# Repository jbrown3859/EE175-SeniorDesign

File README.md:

# EE175-SeniorDesign
Joey Brown, jbrow123 at ucr dot edu  
Merrick Slane, mslan002 at ucr dot edu  
Vincent Le, vle059 at ucr dot edu  

[Google Drive with more material](https://drive.google.com/drive/folders/17umrwFU26v1C86p7LwNFVo5_QjvbGcJk?usp=sharing)

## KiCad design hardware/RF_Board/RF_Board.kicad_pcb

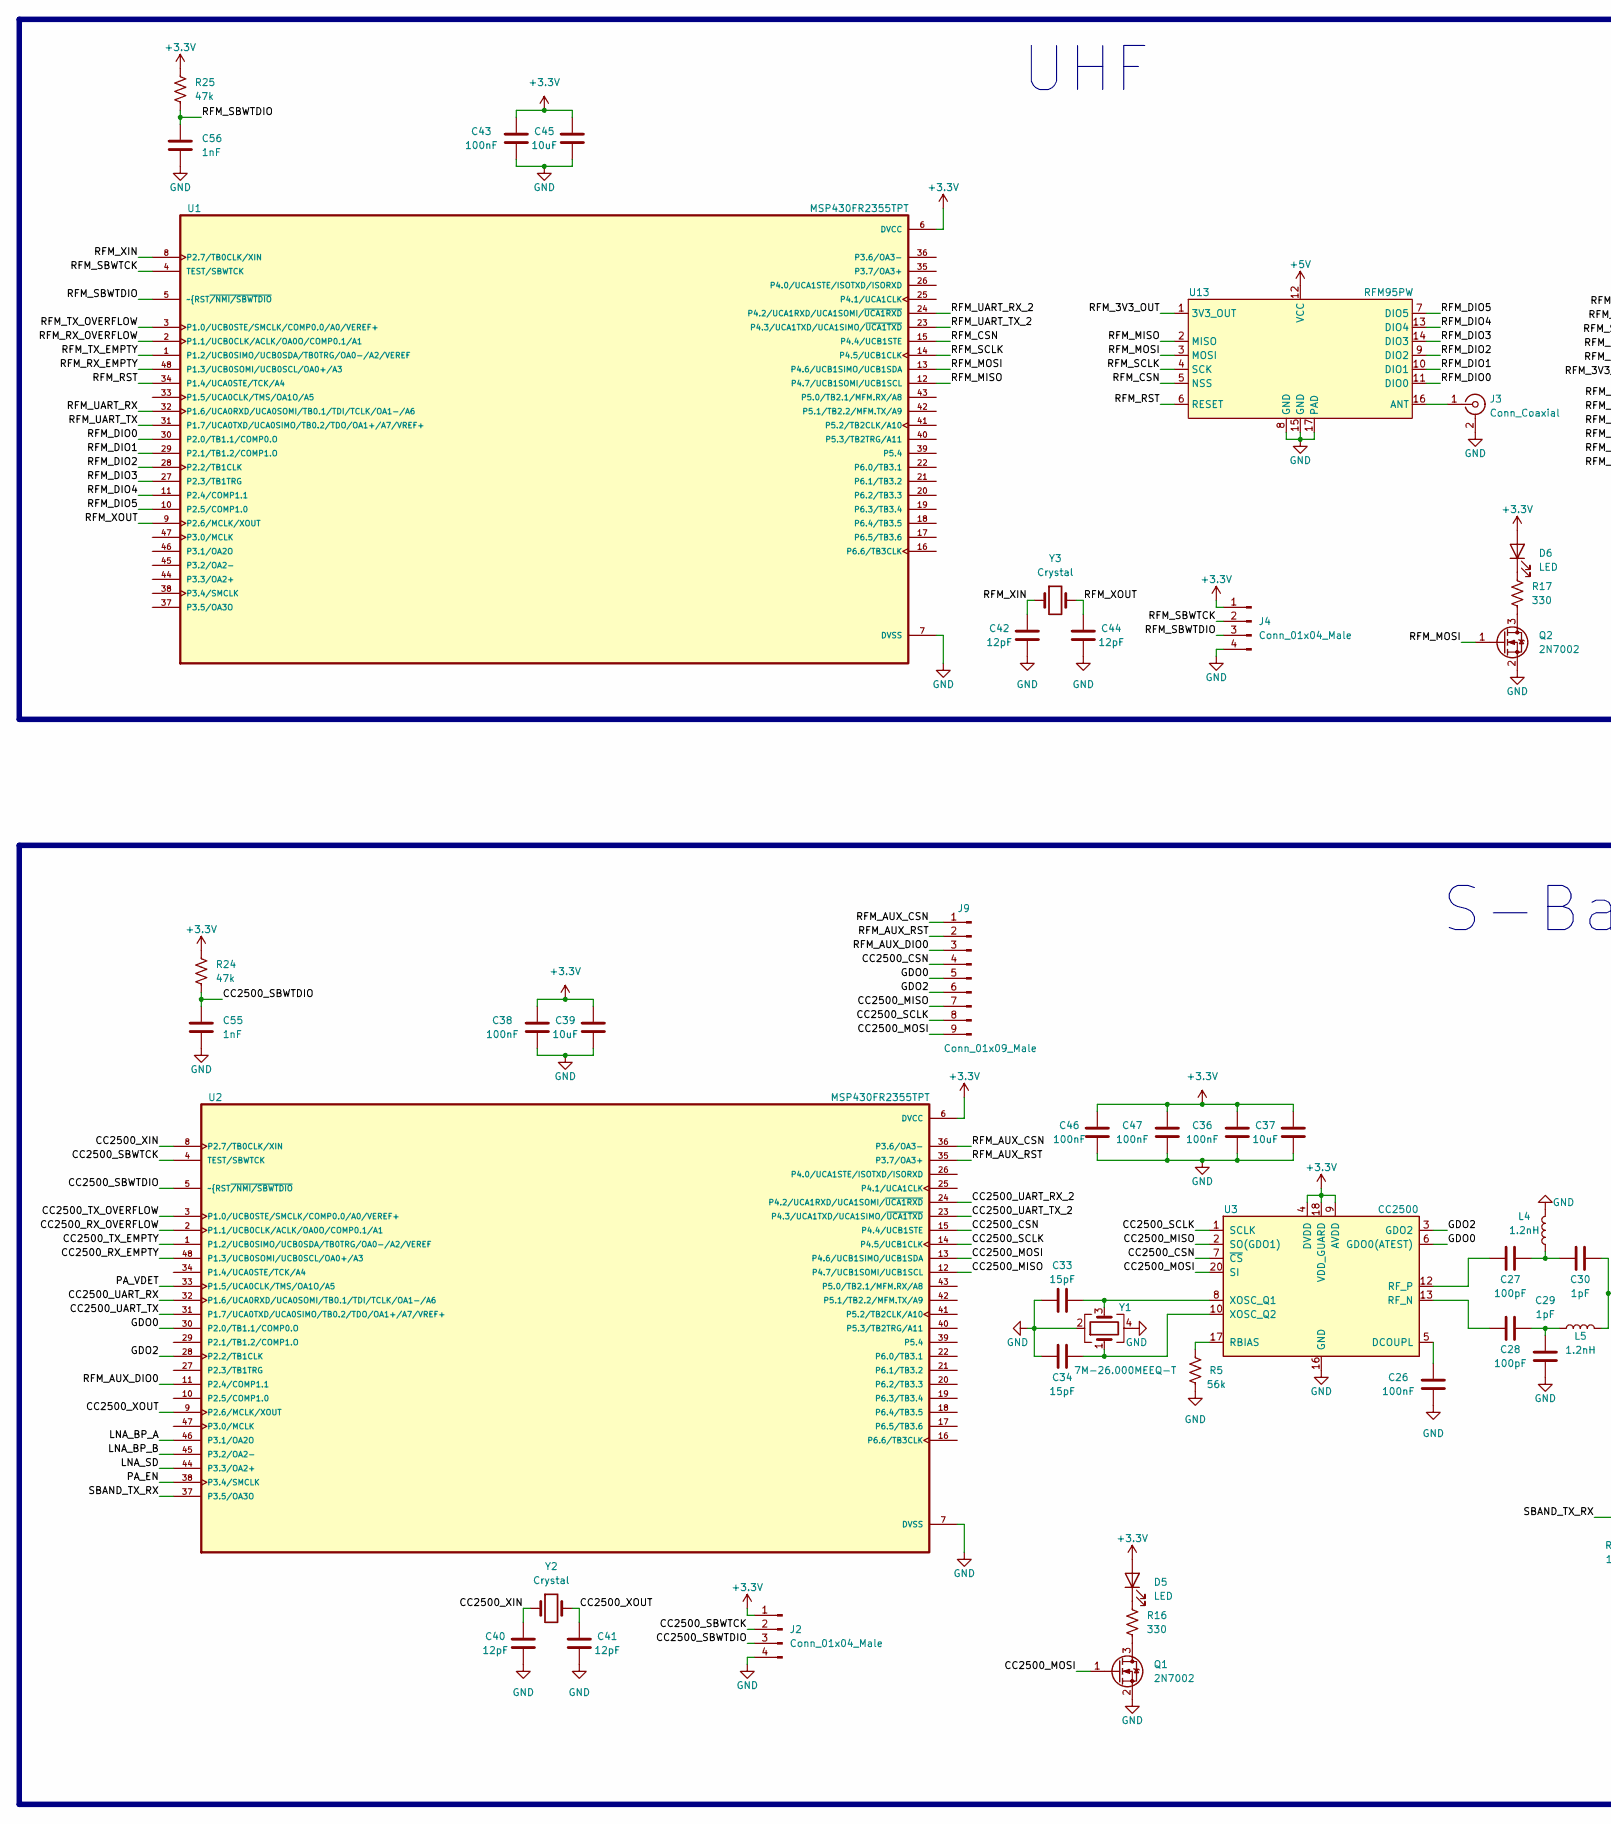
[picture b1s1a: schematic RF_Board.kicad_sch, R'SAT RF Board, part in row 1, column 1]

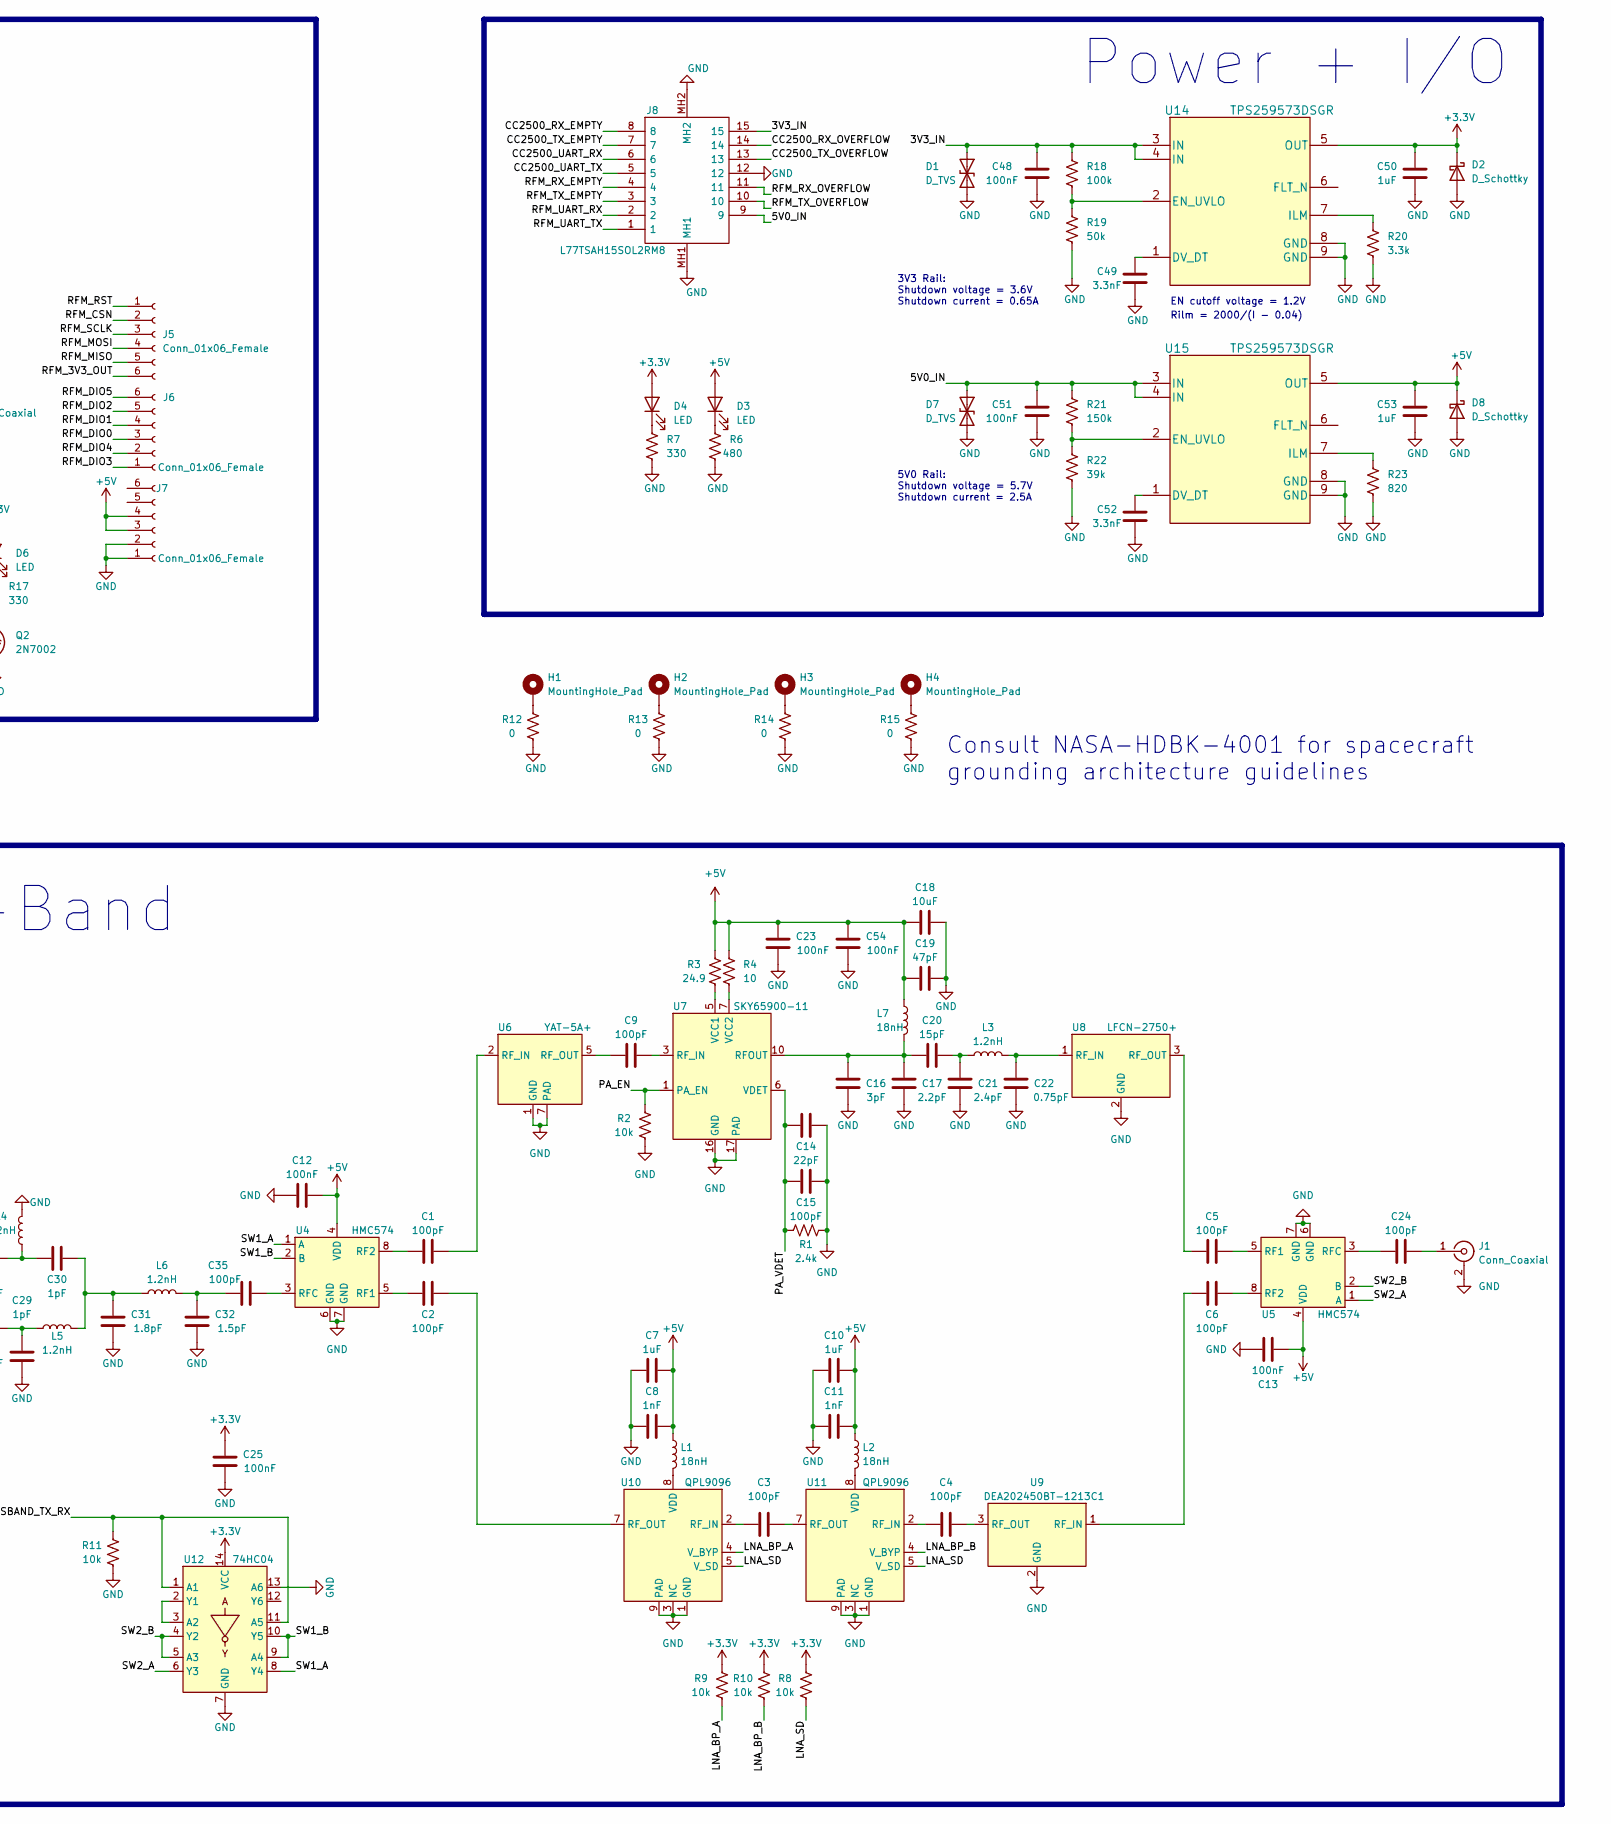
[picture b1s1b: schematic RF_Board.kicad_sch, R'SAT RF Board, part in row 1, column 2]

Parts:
C1, C2, C3, C4, C5, C6, C9, C24, C27, C28, C35: 100pF; C_0402_1005Metric
C7, C10, C50, C53: 1uF; C_0805_2012Metric
C8, C11, C55, C56: 1nF; C_0603_1608Metric
C12, C13, C23, C25, C26, C36, C38, C43, C46, C47, C48, C51, C54: 100nF; C_0603_1608Metric
C14: 22pF; C_0603_1608Metric
C15: 100pF; C_0603_1608Metric
C16: 3pF; C_0402_1005Metric
C17: 2.2pF; C_0402_1005Metric
C18, C37, C39, C45: 10uF; C_1206_3216Metric
C19: 47pF; C_0603_1608Metric
C20: 15pF; C_0402_1005Metric
C21: 2.4pF; C_0402_1005Metric
C22: 0.75pF; C_0402_1005Metric
C29, C30: 1pF; C_0402_1005Metric
C31: 1.8pF; C_0402_1005Metric
C32: 1.5pF; C_0402_1005Metric
C33, C34: 15pF; C_0603_1608Metric
C40, C41, C42, C44: 12pF; C_0603_1608Metric
C49, C52: 3.3nF; C_0603_1608Metric
D1, D7: D_TVS; SOD882
D2, D8: D_Schottky; D_SOD-523
D3, D4, D5, D6: LED; LED_0603_1608Metric
H1, H2, H3, H4: MountingHole_Pad; MountingHole_4.3mm_M4_Pad_Via
J1, J3: Conn_Coaxial; SMA_Amphenol_901-144_Vertical
J2, J4: Conn_01x04_Male; PinHeader_1x04_P2.54mm_Vertical
J5, J6, J7: Conn_01x06_Female; PinHeader_1x06_P2.54mm_Vertical
J8: L77TSAH15SOL2RM8; Mouser Part Number 523-L77TSAH15SOL2RM8
J9: Conn_01x09_Male; PinHeader_1x09_P2.54mm_Vertical
L1, L2, L7: 18nH; L_0603_1608Metric
L3, L4, L5, L6: 1.2nH; L_0402_1005Metric
Q1, Q2: 2N7002; SOT-23
R1: 2.4k; R_0603_1608Metric
R2, R8, R9, R10, R11: 10k; R_0603_1608Metric
R3: 24.9; R_0603_1608Metric
R4: 10; R_0603_1608Metric
R5: 56k; C_0603_1608Metric
R6: 480; R_0603_1608Metric
R7, R16, R17: 330; R_0603_1608Metric
R12, R13, R14, R15: 0; R_0603_1608Metric
R18: 100k; R_0402_1005Metric
R19: 50k; R_0402_1005Metric
R20: 3.3k; R_0402_1005Metric
R21: 150k; R_0402_1005Metric
R22: 39k; R_0402_1005Metric
R23: 820; R_0402_1005Metric
R24, R25: 47k; R_0603_1608Metric
U1, U2: MSP430FR2355TPT; QFP50P900X900X160-48N
U3: CC2500; Texas_S-PVQFN-N20_EP2.4x2.4mm
U4, U5: HMC574; HMC574AMS8E
U6: YAT-5A+; YAT-1A&plus_
U7: SKY65900-11; QFN-16-1EP_4x4mm_P0.65mm_EP2.5x2.5mm
U8: LFCN-2750+; LFCN-2500&plus_
U9: DEA202450BT-1213C1
U10, U11: QPL9096; QPL9504TR7
U12: 74HC04; SOIC-14_3.9x8.7mm_P1.27mm
U13: RFM95PW
U14, U15: TPS259573DSGR; DSG0008A
Y1: 7M-26.000MEEQ-T; Crystal_SMD_3225-4Pin_3.2x2.5mm
Y2, Y3: Crystal; ECS-.327-12.5-34B-TR

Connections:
+3.3V: C25.1, C36.1, C37.2, C38.1, C39.2, C43.1, C45.2, C46.2, C47.1, C50.2, D2.1 (K), D4.2 (A), D5.2 (A), D6.2 (A), J2.1, J4.1, R8.1, R9.1, R10.1, R24.1, R25.1, U1.6 (DVCC), U2.6 (DVCC), U3.4 (DVDD), U3.9 (AVDD), U3.11 (AVDD), U3.14 (AVDD), U3.15 (AVDD), U3.18 (VDD_GUARD), U12.14 (VCC), U14.5 (OUT)
+5V: C7.2, C8.2, C10.2, C11.2, C12.1, C13.1, C18.1, C19.1, C23.1, C53.2, C54.1, D3.2 (A), D8.1 (K), J7.3, J7.4, L1.1, L2.1, L7.1, R3.1, R4.2, U4.4 (VDD), U5.4 (VDD), U13.12 (VCC), U15.5 (OUT)
/3V3_IN: C48.1, D1.1 (A1), J8.15, R18.1, U14.3 (IN), U14.4 (IN)
/5V0_IN: C51.1, D7.1 (A1), J8.9, R21.1, U15.3 (IN), U15.4 (IN)
/CC2500_CSN: J9.4, U2.15 (P4.4/UCB1STE), U3.7 (~CS)
/CC2500_MISO: J9.7, U2.12 (P4.7/UCB1SOMI/UCB1SCL), U3.2 (SO(GDO1))
/CC2500_MOSI: J9.9, Q1.1 (G), U2.13 (P4.6/UCB1SIMO/UCB1SDA), U3.20 (SI)
/CC2500_RX_EMPTY: J8.8, U2.48 (P1.3/UCB0SOMI/UCB0SCL/OA0+/A3)
/CC2500_RX_OVERFLOW: J8.14, U2.2 (P1.1/UCB0CLK/ACLK/OA0O/COMP0.1/A1)
/CC2500_SBWTCK: J2.2, U2.4 (TEST/SBWTCK)
/CC2500_SBWTDIO: C55.1, J2.3, R24.2, U2.5 (~RST~{/NMI/SBWTDIO)
/CC2500_SCLK: J9.8, U2.14 (P4.5/UCB1CLK), U3.1 (SCLK)
/CC2500_TX_EMPTY: J8.7, U2.1 (P1.2/UCB0SIMO/UCB0SDA/TB0TRG/OA0-/A2/VE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)
/CC2500_TX_OVERFLOW: J8.13, U2.3 (P1.0/UCB0STE/SMCLK/COMP0.0/A0/VEREF+)
/CC2500_UART_RX: J8.6, U2.32 (P1.6/UCA0RXD/UCA0SOMI/TB0.1/TDI/TCLK/OA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)
/CC2500_UART_RX_2: U2.24 (P4.2/UCA1RXD/UCA1SOMI/~UCA1RXD)
/CC2500_UART_TX: J8.5, U2.31 (P1.7/UCA0TXD/UCA0SIMO/TB0.2/TDO/OA1+/A7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)
/CC2500_UART_TX_2: U2.23 (P4.3/UCA1TXD/UCA1SIMO/~UCA1TXD)
/CC2500_XIN: C40.2, U2.8 (P2.7/TB0CLK/XIN), Y2.1
/CC2500_XOUT: C41.2, U2.9 (P2.6/MCLK/XOUT), Y2.2
/GDO0: J9.5, U2.30 (P2.0/TB1.1/COMP0.O), U3.6 (GDO0(ATEST))
/GDO2: J9.6, U2.28 (P2.2/TB1CLK), U3.3 (GDO2)
/LNA_BP_A: R9.2, U2.46 (P3.1/OA2O), U10.4 (V_BYP)
/LNA_BP_B: R10.2, U2.45 (P3.2/OA2-), U11.4 (V_BYP)
/LNA_SD: R8.2, U2.44 (P3.3/OA2+), U10.5 (V_SD), U11.5 (V_SD)
/PA_EN: R2.1, U2.38 (P3.4/SMCLK), U7.1 (PA_EN)
/PA_VDET: C14.1, C15.1, R1.1, U2.33 (P1.5/UCA0CLK/TMS/OA1O/A5), U7.6 (VDET)
/RFM_3V3_OUT: J5.6, U13.1 (3V3_OUT)
/RFM_AUX_CSN: J9.1, U2.36 (P3.6/OA3-)
/RFM_AUX_DIO0: J9.3, U2.11 (P2.4/COMP1.1)
/RFM_AUX_RST: J9.2, U2.35 (P3.7/OA3+)
/RFM_CSN: J5.2, U1.15 (P4.4/UCB1STE), U13.5 (NSS)
/RFM_DIO0: J6.3, U1.30 (P2.0/TB1.1/COMP0.O), U13.11 (DIO0)
/RFM_DIO1: J6.4, U1.29 (P2.1/TB1.2/COMP1.O), U13.10 (DIO1)
/RFM_DIO2: J6.5, U1.28 (P2.2/TB1CLK), U13.9 (DIO2)
/RFM_DIO3: J6.1, U1.27 (P2.3/TB1TRG), U13.14 (DIO3)
/RFM_DIO4: J6.2, U1.11 (P2.4/COMP1.1), U13.13 (DIO4)
/RFM_DIO5: J6.6, U1.10 (P2.5/COMP1.0), U13.7 (DIO5)
/RFM_MISO: J5.5, U1.12 (P4.7/UCB1SOMI/UCB1SCL), U13.2 (MISO)
/RFM_MOSI: J5.4, Q2.1 (G), U1.13 (P4.6/UCB1SIMO/UCB1SDA), U13.3 (MOSI)
/RFM_RST: J5.1, U1.34 (P1.4/UCA0STE/TCK/A4), U13.6 (RESET)
/RFM_RX_EMPTY: J8.4, U1.48 (P1.3/UCB0SOMI/UCB0SCL/OA0+/A3)
/RFM_RX_OVERFLOW: J8.11, U1.2 (P1.1/UCB0CLK/ACLK/OA0O/COMP0.1/A1)
/RFM_SBWTCK: J4.2, U1.4 (TEST/SBWTCK)
/RFM_SBWTDIO: C56.1, J4.3, R25.2, U1.5 (~RST~{/NMI/SBWTDIO)
/RFM_SCLK: J5.3, U1.14 (P4.5/UCB1CLK), U13.4 (SCK)
/RFM_TX_EMPTY: J8.3, U1.1 (P1.2/UCB0SIMO/UCB0SDA/TB0TRG/OA0-/A2/VE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)
/RFM_TX_OVERFLOW: J8.10, U1.3 (P1.0/UCB0STE/SMCLK/COMP0.0/A0/VEREF+)
/RFM_UART_RX: J8.2, U1.32 (P1.6/UCA0RXD/UCA0SOMI/TB0.1/TDI/TCLK/OA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)
/RFM_UART_RX_2: U1.24 (P4.2/UCA1RXD/UCA1SOMI/~UCA1RXD)
/RFM_UART_TX: J8.1, U1.31 (P1.7/UCA0TXD/UCA0SIMO/TB0.2/TDO/OA1+/A7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)
/RFM_UART_TX_2: U1.23 (P4.3/UCA1TXD/UCA1SIMO/~UCA1TXD)
/RFM_XIN: C42.2, U1.8 (P2.7/TB0CLK/XIN), Y3.1; also elsewhere on the board
/RFM_XOUT: C44.2, U1.9 (P2.6/MCLK/XOUT), Y3.2; also elsewhere on the board
/SBAND_TX_RX: R11.1, U2.37 (P3.5/OA3O), U12.1 (A1), U12.11 (A5)
/SW1_A: U4.1 (A), U12.8 (Y4)
/SW1_B: U4.2 (B), U12.9 (A4), U12.10 (Y5)
/SW2_A: U5.1 (A), U12.6 (Y3)
/SW2_B: U5.2 (B), U12.4 (Y2), U12.5 (A3)
GND: C7.1, C8.1, C10.1, C11.1, C12.2, C13.2, C14.2, C15.2, C16.2, C17.2, C18.2, C19.2, C21.1, C22.1, C23.2, C25.2, C26.2, C29.1, C31.1, C32.1, C33.1, C34.1, C36.2, C37.1, C38.2, C39.1, C40.1, C41.1, C42.1, C43.2, C44.1, C45.1, C46.1, C47.2, C48.2, C49.2, C50.1, C51.2, C52.2, C53.1, C54.2, C55.2, C56.2, D1.2 (A2), D2.2 (A), D7.2 (A2), D8.2 (A), J1.2 (Ext), J2.4, J3.2 (Ext), J4.4, J7.1, J7.2, J8.12, J8.MH1, J8.MH2, L4.2, Q1.2 (S), Q2.2 (S), R1.2, R2.2, R5.2, R6.2, R7.2, R11.2, R12.2, R13.2, R14.2, R15.2, R19.2, R20.2, R22.2, R23.2, U1.7 (DVSS), U2.7 (DVSS), U3.16 (GND), U3.19 (GND), U3.21 (GND), U4.6 (GND), U4.7 (GND), U5.6 (GND), U5.7 (GND), U6.1 (GND), U6.3 (GND), U6.4 (GND), U6.6 (GND), U6.7 (PAD), U7.2 (GND), U7.4 (GND), U7.8 (GND), U7.9 (GND), U7.12 (GND), U7.13 (GND), U7.14 (GND), U7.15 (GND), U7.16 (GND), U7.17 (PAD), U8.2 (GND), U8.4 (GND), U9.2 (GND), U9.4 (GND), U10.1 (GND), U10.3 (NC), U10.6 (GND), U10.9 (PAD), U11.1 (GND), U11.3 (NC), U11.6 (GND), U11.9 (PAD), U12.7 (GND), U12.13 (A6), U13.8 (GND), U13.15 (GND), U13.17 (PAD), U14.8 (GND), U14.9 (GND), U15.8 (GND), U15.9 (GND), Y1.2, Y1.4
unnamed: C1.1, U4.8 (RF2)
unnamed: C1.2, U6.2 (RF_IN)
unnamed: C2.1, U4.5 (RF1)
unnamed: C2.2, U10.7 (RF_OUT)
unnamed: C3.1, U10.2 (RF_IN)
unnamed: C3.2, U11.7 (RF_OUT)
unnamed: C4.1, U11.2 (RF_IN)
unnamed: C4.2, U9.3 (RF_OUT)
unnamed: C5.1, U8.3 (RF_OUT)
unnamed: C5.2, U5.5 (RF1)
unnamed: C6.1, U9.1 (RF_IN)
unnamed: C6.2, U5.8 (RF2)
unnamed: C9.1, U6.5 (RF_OUT)
unnamed: C9.2, U7.3 (RF_IN)
unnamed: C16.1, C17.1, C20.1, L7.2, U7.10 (RFOUT), U7.11 (RFOUT)
unnamed: C20.2, C21.2, L3.1
unnamed: C22.2, L3.2, U8.1 (RF_IN)
unnamed: C24.1, U5.3 (RFC)
unnamed: C24.2, J1.1 (In)
unnamed: C26.1, U3.5 (DCOUPL)
unnamed: C27.1, U3.12 (RF_P)
unnamed: C27.2, C30.1, L4.1
unnamed: C28.1, U3.13 (RF_N)
unnamed: C28.2, C29.2, L5.1
unnamed: C30.2, C31.2, L5.2, L6.1
unnamed: C32.2, C35.1, L6.2
unnamed: C35.2, U4.3 (RFC)
unnamed: C49.1, U14.1 (DV_DT)
unnamed: C52.1, U15.1 (DV_DT)
unnamed: D3.1 (K), R6.1
unnamed: D4.1 (K), R7.1
unnamed: D5.1 (K), R16.1
unnamed: D6.1 (K), R17.1
unnamed: H1.1, R12.1
unnamed: H2.1, R13.1
unnamed: H3.1, R14.1
unnamed: H4.1, R15.1
unnamed: J3.1 (In), U13.16 (ANT)
unnamed: L1.2, U10.8 (VDD)
unnamed: L2.2, U11.8 (VDD)
unnamed: Q1.3 (D), R16.2
unnamed: Q2.3 (D), R17.2
unnamed: R3.2, U7.5 (VCC1)
unnamed: R4.1, U7.7 (VCC2)
unnamed: R5.1, U3.17 (RBIAS)
unnamed: R18.2, R19.1, U14.2 (EN_UVLO)
unnamed: R20.1, U14.7 (ILM)
unnamed: R21.2, R22.1, U15.2 (EN_UVLO)
unnamed: R23.1, U15.7 (ILM)
unnamed: C34.2, U3.10 (XOSC_Q2), Y1.1
unnamed: U12.2 (Y1), U12.3 (A2)
unnamed: C33.2, U3.8 (XOSC_Q1), Y1.3

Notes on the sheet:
S-Band
Rilm = 2000/(I - 0.04)
5V0 Rail: Shutdown voltage = 5.7V Shutdown current = 2.5A
EN cutoff voltage = 1.2V
Consult NASA-HDBK-4001 for spacecraft grounding architecture guidelines
Power + I/O
3V3 Rail: Shutdown voltage = 3.6V Shutdown current = 0.65A
UHF

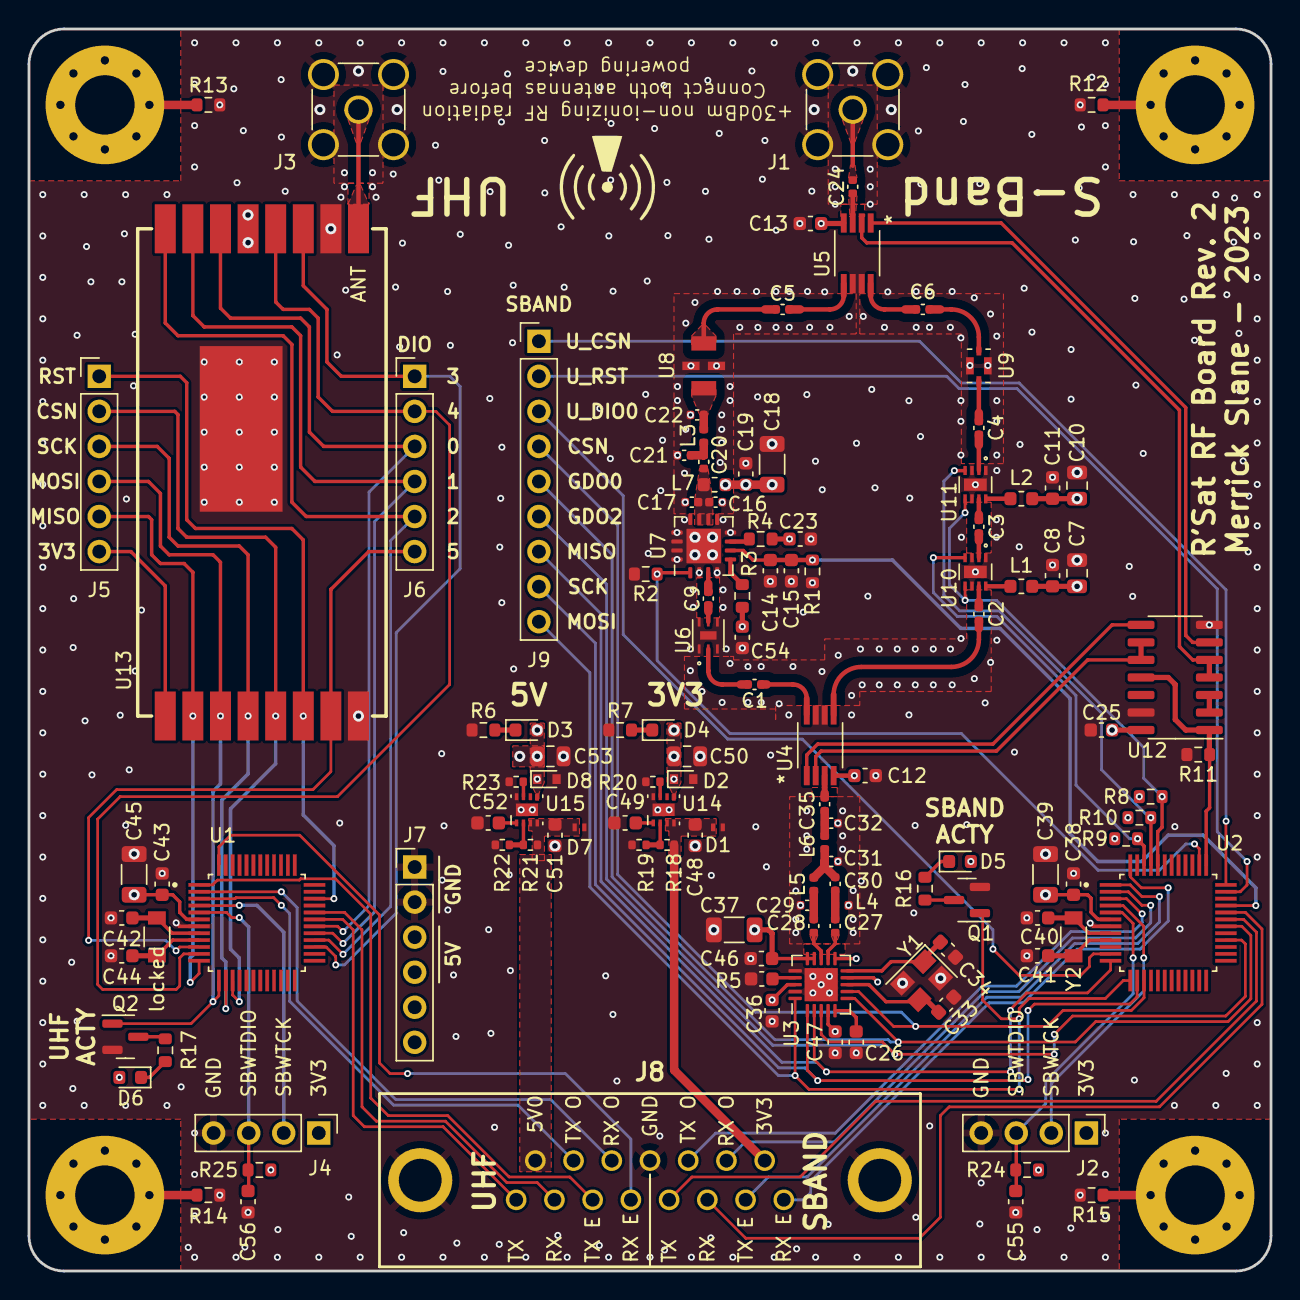
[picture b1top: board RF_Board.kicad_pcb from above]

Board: 4 copper layers, 90.0 x 90.0 mm, 129 parts (0 on the bottom side), 108 nets.

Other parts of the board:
locked: Crystal; ECS-.327-12.5-34B-TR

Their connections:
/RFM_XIN: locked.1; also elsewhere on the board
/RFM_XOUT: locked.2; also elsewhere on the board

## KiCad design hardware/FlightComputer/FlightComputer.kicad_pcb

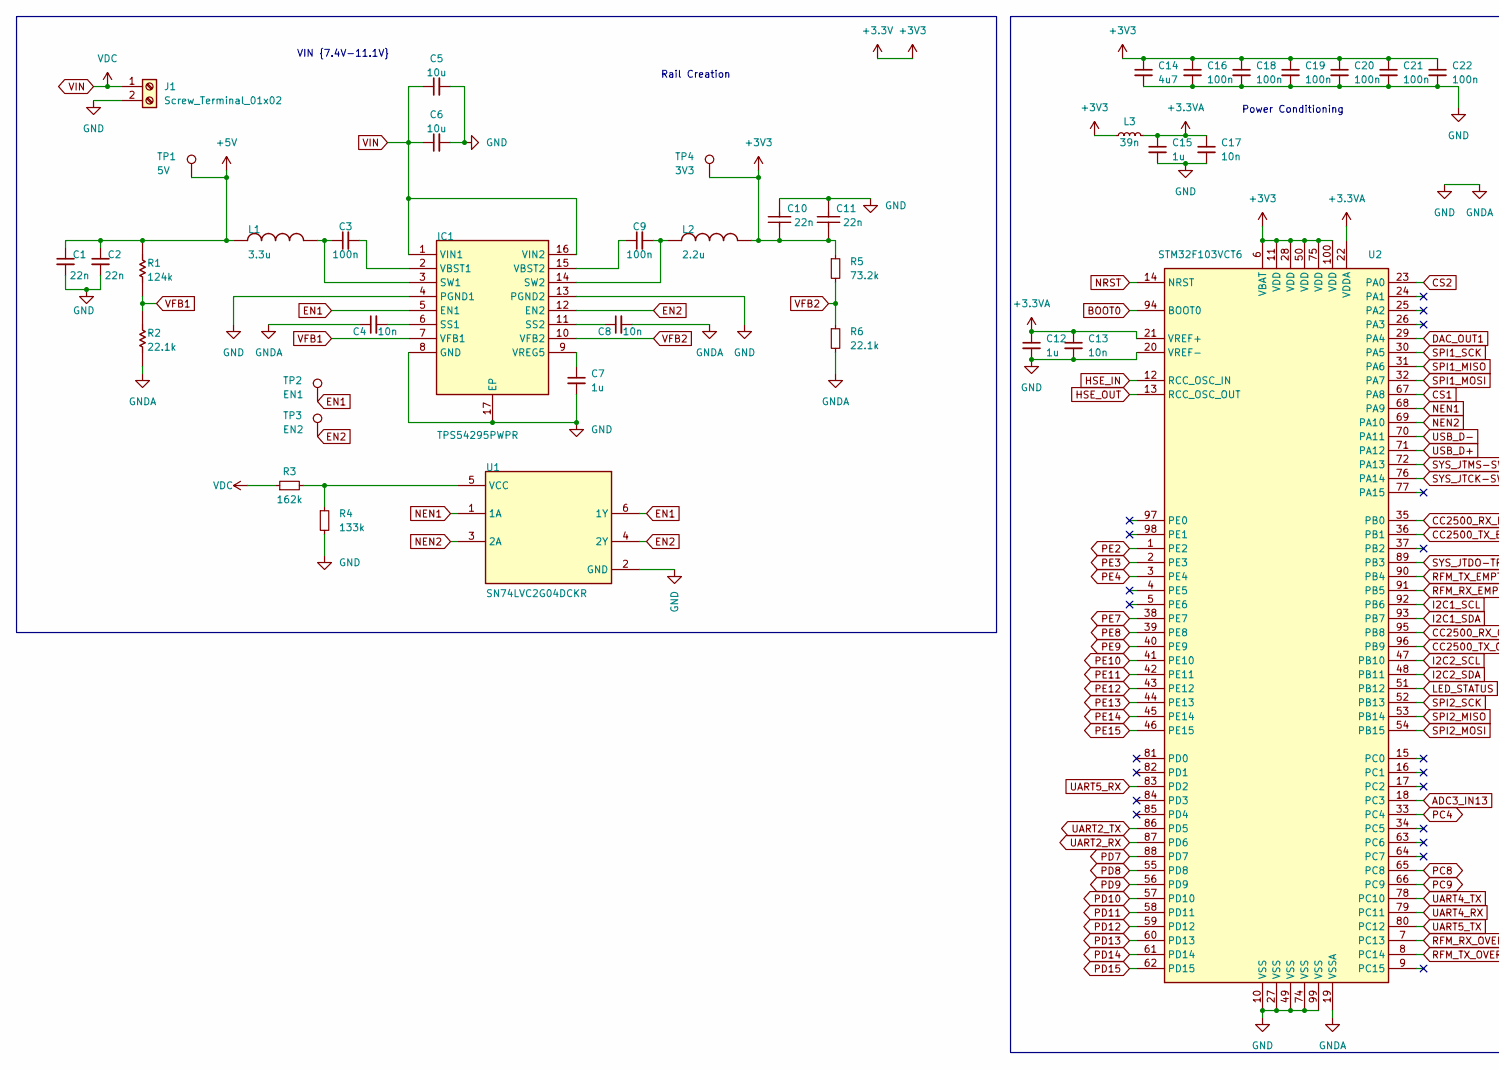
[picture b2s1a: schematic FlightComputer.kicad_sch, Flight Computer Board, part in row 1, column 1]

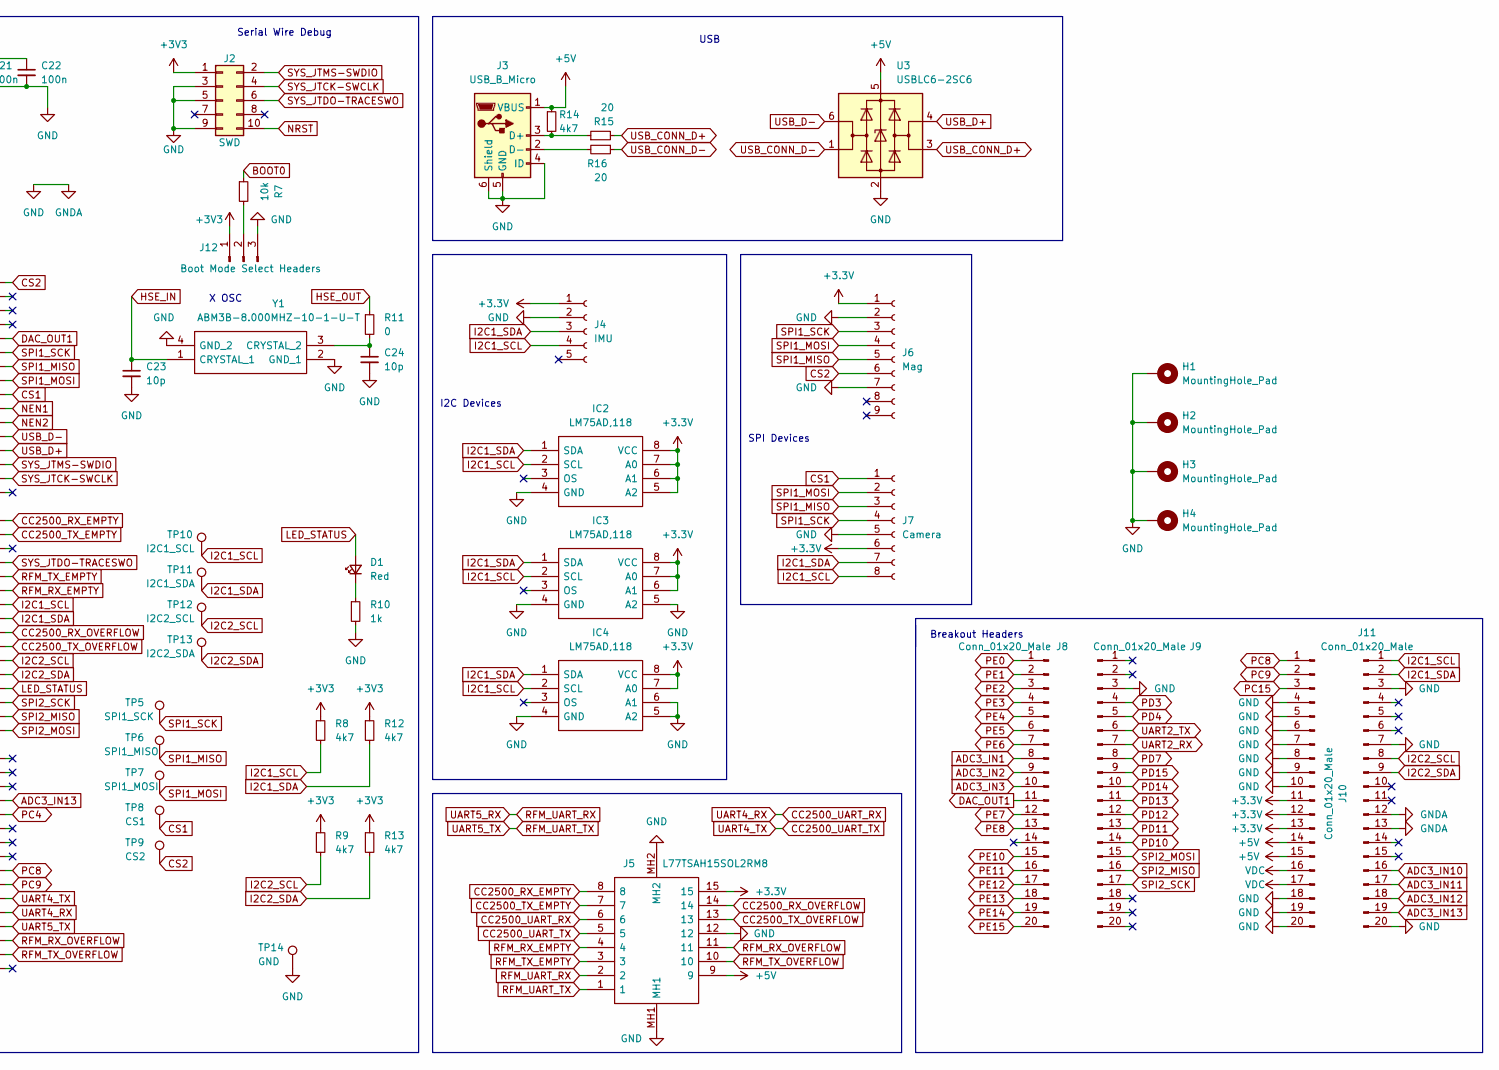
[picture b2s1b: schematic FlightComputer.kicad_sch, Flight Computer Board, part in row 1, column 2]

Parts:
C1, C2, C10, C11: 22n; C_0603_1608Metric_Pad1.08x0.95mm_HandSolder
C3, C9, C16, C18, C19, C20, C21, C22: 100n; C_0603_1608Metric_Pad1.08x0.95mm_HandSolder
C4, C8, C13, C17: 10n; C_0603_1608Metric_Pad1.08x0.95mm_HandSolder
C5, C6: 10u; C_1206_3216Metric_Pad1.33x1.80mm_HandSolder
C7, C12, C15: 1u; C_0603_1608Metric_Pad1.08x0.95mm_HandSolder
C14: 4u7; C_0603_1608Metric_Pad1.08x0.95mm_HandSolder
C23, C24: 10p; C_0603_1608Metric_Pad1.08x0.95mm_HandSolder
D1: Red; LED_0603_1608Metric_Pad1.05x0.95mm_HandSolder
H1, H2, H3, H4: MountingHole_Pad; MountingHole_4.3mm_M4_Pad_Via
IC1: TPS54295PWPR; HTSSOP-16-1EP_4.4x5mm_P0.65mm_EP3.4x5mm_Mask2.46x2.31mm_The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; MANUFACTURER_PART_NUMBER TPS54295PWPR; MOUSER PART NUMBER 595-TPS54295PWPR
IC2, IC3, IC4: LM75AD,118; SOIC-8-1EP_3.9x4.9mm_P1.27mm_EP2.29x3mm_ThermalVias; Mouser Part Number 771-LM75AD-T
J1: Screw_Terminal_01x02; Altech_AK300_1x02_P5.00mm_45-Degree
J2: SWD; PinSocket_2x05_P1.27mm_Vertical_SMD
J3: USB_B_Micro; USB_Micro-B_Molex_47346-0001
J4: IMU; PinHeader_1x05_P2.54mm_Vertical
J5: L77TSAH15SOL2RM8; DSUB-15_Female_Vertical_P2.77x2.84mm_MountingHoles; Mouser Part Number 523-L77TSAH15SOL2RM8
J6: Mag; PinSocket_1x09_P2.54mm_Vertical
J7: Camera; PinHeader_1x08_P2.54mm_Vertical
J8, J9, J10, J11: Conn_01x20_Male; PinHeader_1x20_P2.54mm_Vertical
J12: Boot Mode Select Headers; PinHeader_1x03_P2.54mm_Vertical
L1: 3.3u; L_1812_4532Metric_Pad1.30x3.40mm_HandSolder
L2: 2.2u; L_1812_4532Metric_Pad1.30x3.40mm_HandSolder
L3: 39n; L_0603_1608Metric_Pad1.05x0.95mm_HandSolder
R1: 124k; R_0603_1608Metric_Pad0.98x0.95mm_HandSolder
R2, R6: 22.1k; R_0603_1608Metric_Pad0.98x0.95mm_HandSolder
R3: 162k; R_0603_1608Metric_Pad0.98x0.95mm_HandSolder
R4: 133k; R_0603_1608Metric_Pad0.98x0.95mm_HandSolder
R5: 73.2k; R_0603_1608Metric_Pad0.98x0.95mm_HandSolder
R7: 10k; R_0603_1608Metric_Pad0.98x0.95mm_HandSolder
R8, R9, R12, R13, R14: 4k7; R_0603_1608Metric_Pad0.98x0.95mm_HandSolder
R10: 1k; R_0603_1608Metric_Pad0.98x0.95mm_HandSolder
R11: 0; R_0603_1608Metric_Pad0.98x0.95mm_HandSolder
R15, R16: 20; R_0603_1608Metric_Pad0.98x0.95mm_HandSolder
TP1: 5V; TestPoint_Keystone_5015_Micro-Minature
TP2: EN1; TestPoint_Keystone_5015_Micro-Minature
TP3: EN2; TestPoint_Keystone_5015_Micro-Minature
TP4: 3V3; TestPoint_Keystone_5015_Micro-Minature
TP5: SPI1_SCK; TestPoint_Keystone_5015_Micro-Minature
TP6: SPI1_MISO; TestPoint_Keystone_5015_Micro-Minature
TP7: SPI1_MOSI; TestPoint_Keystone_5015_Micro-Minature
TP8: CS1; TestPoint_Keystone_5015_Micro-Minature
TP9: CS2; TestPoint_Keystone_5015_Micro-Minature
TP10: I2C1_SCL; TestPoint_Keystone_5015_Micro-Minature
TP11: I2C1_SDA; TestPoint_Keystone_5015_Micro-Minature
TP12: I2C2_SCL; TestPoint_Keystone_5015_Micro-Minature
TP13: I2C2_SDA; TestPoint_Keystone_5015_Micro-Minature
TP14: GND; TestPoint_Keystone_5015_Micro-Minature
U1: SN74LVC2G04DCKR; WSON-6_1.5x1.5mm_P0.5mm
U2: STM32F103VCT6; LQFP-100_14x14mm_P0.5mm
U3: USBLC6-2SC6; SOT-23-6
Y1: ABM3B-8.000MHZ-10-1-U-T; Crystal_SMD_Abracon_ABM3B-4Pin_5.0x3.2mm; Mouser Part Number 815-ABM3B8MHZ101UT

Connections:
+3.3V: C10.1, C11.1, C14.1, C16.1, C18.1, C19.1, C20.1, C21.1, C22.1, IC2.5 (A2), IC2.6 (A1), IC2.7 (A0), IC2.8 (VCC), IC3.6 (A1), IC3.7 (A0), IC3.8 (VCC), IC4.7 (A0), IC4.8 (VCC), J2.1, J4.1, J5.15, J6.1, J7.6, J10.11, J10.12, J10.13, J12.1, L2.2, L3.1, R5.1, R8.1, R9.1, R12.1, R13.1, TP4.1, U2.6 (VBAT), U2.11 (VDD), U2.28 (VDD), U2.50 (VDD), U2.75 (VDD), U2.100 (VDD)
+3.3VA: C12.1, C13.1, C15.1, C17.1, L3.2, U2.21 (VREF+), U2.22 (VDDA)
+5V: C1.1, C2.1, J3.1 (VBUS), J5.9, J10.14, J10.15, L1.1, R1.1, R14.1, TP1.1, U3.5 (VBUS)
ADC3_IN1: J8.8
ADC3_IN2: J8.9
ADC3_IN3: J8.10
ADC3_IN10: J11.16
ADC3_IN11: J11.17
ADC3_IN12: J11.18
ADC3_IN13: J11.19, U2.18 (PC3)
BOOT0: R7.1, U2.94 (BOOT0)
CC2500_RX_EMPTY: J5.8, U2.35 (PB0)
CC2500_RX_OVERFLOW: J5.14, U2.95 (PB8)
CC2500_TX_EMPTY: J5.7, U2.36 (PB1)
CC2500_TX_OVERFLOW: J5.13, U2.96 (PB9)
CC2500_UART_RX: J5.6, U2.79 (PC11)
CC2500_UART_TX: J5.5, U2.78 (PC10)
CS1: J7.1, TP8.1, U2.67 (PA8)
CS2: J6.6, TP9.1, U2.23 (PA0)
DAC_OUT1: J8.11, U2.29 (PA4)
EN1: IC1.5 (EN1), TP2.1, U1.6 (1Y)
EN2: IC1.12 (EN2), TP3.1, U1.4 (2Y)
GND: C1.2, C2.2, C4.1, C5.2, C6.2, C7.2, C8.2, C10.2, C11.2, C12.2, C13.2, C14.2, C15.2, C16.2, C17.2, C18.2, C19.2, C20.2, C21.2, C22.2, C23.2, C24.2, H1.1, H2.1, H3.1, H4.1, IC1.4 (PGND1), IC1.8 (GND), IC1.13 (PGND2), IC1.17 (EP), IC2.4 (GND), IC3.4 (GND), IC3.5 (A2), IC4.4 (GND), IC4.5 (A2), IC4.6 (A1), J1.2, J2.3, J2.5, J2.9, J3.4 (ID), J3.5 (GND), J3.6 (Shield), J4.2, J5.12, J5.MH1, J5.MH2, J6.2, J6.7, J7.5, J9.3, J10.4, J10.5, J10.6, J10.7, J10.8, J10.9, J10.10, J10.18, J10.19, J10.20, J11.3, J11.7, J11.12, J11.13, J11.20, J12.3, R2.2, R4.2, R6.2, R10.2, TP14.1, U1.2 (GND), U2.10 (VSS), U2.19 (VSSA), U2.20 (VREF-), U2.27 (VSS), U2.49 (VSS), U2.74 (VSS), U2.99 (VSS), U3.2 (GND), Y1.2 (GND_1), Y1.4 (GND_2); also elsewhere on the board
HSE_IN: C23.1, U2.12 (RCC_OSC_IN), Y1.1 (CRYSTAL_1)
HSE_OUT: R11.1, U2.13 (RCC_OSC_OUT)
I2C1_SCL: IC2.2 (SCL), IC3.2 (SCL), IC4.2 (SCL), J4.4, J7.8, J11.1, R8.2, TP10.1, U2.92 (PB6)
I2C1_SDA: IC2.1 (SDA), IC3.1 (SDA), IC4.1 (SDA), J4.3, J7.7, J11.2, R12.2, TP11.1, U2.93 (PB7)
I2C2_SCL: J11.8, R9.2, TP12.1, U2.47 (PB10)
I2C2_SDA: J11.9, R13.2, TP13.1, U2.48 (PB11)
LED_STATUS: D1.2 (A), U2.51 (PB12)
NEN1: U1.1 (1A), U2.68 (PA9)
NEN2: U1.3 (2A), U2.69 (PA10)
NRST: J2.10, U2.14 (NRST)
unnamed: C3.1, IC1.3 (SW1), L1.2
unnamed: C3.2, IC1.2 (VBST1)
unnamed: C4.2, IC1.6 (SS1)
unnamed: C7.1, IC1.9 (VREG5)
unnamed: C8.1, IC1.11 (SS2)
unnamed: C9.1, IC1.15 (VBST2)
unnamed: C9.2, IC1.14 (SW2), L2.1
unnamed: C24.1, R11.2, Y1.3 (CRYSTAL_2)
unnamed: D1.1 (K), R10.1
unnamed: J3.2 (D-), R16.2
unnamed: J3.3 (D+), R14.2, R15.1
unnamed: J12.2, R7.2
unnamed: R3.2, R4.1, U1.5 (VCC)
PC4: U2.33 (PC4)
PC8: J10.1, U2.65 (PC8)
PC9: J10.2, U2.66 (PC9)
PC15: J10.3
PD3: J9.4
PD4: J9.5
PD7: J9.8, U2.88 (PD7)
PD8: U2.55 (PD8)
PD9: U2.56 (PD9)
PD10: J9.14, U2.57 (PD10)
PD11: J9.13, U2.58 (PD11)
PD12: J9.12, U2.59 (PD12)
PD13: J9.11, U2.60 (PD13)
PD14: J9.10, U2.61 (PD14)
PD15: J9.9, U2.62 (PD15)
PE0: J8.1
PE1: J8.2
PE2: J8.3, U2.1 (PE2)
PE3: J8.4, U2.2 (PE3)
PE4: J8.5, U2.3 (PE4)
PE5: J8.6
PE6: J8.7
PE7: J8.12, U2.38 (PE7)
PE8: J8.13, U2.39 (PE8)
PE9: U2.40 (PE9)
PE10: J8.15, U2.41 (PE10)
PE11: J8.16, U2.42 (PE11)
PE12: J8.17, U2.43 (PE12)
PE13: J8.18, U2.44 (PE13)
PE14: J8.19, U2.45 (PE14)
PE15: J8.20, U2.46 (PE15)
RFM_RX_EMPTY: J5.4, U2.91 (PB5)
RFM_RX_OVERFLOW: J5.11, U2.7 (PC13)
RFM_TX_EMPTY: J5.3, U2.90 (PB4)
RFM_TX_OVERFLOW: J5.10, U2.8 (PC14)
RFM_UART_RX: J5.2, U2.83 (PD2)
RFM_UART_TX: J5.1, U2.80 (PC12)
SPI1_MISO: J6.5, J7.3, TP6.1, U2.31 (PA6)
SPI1_MOSI: J6.4, J7.2, TP7.1, U2.32 (PA7)
SPI1_SCK: J6.3, J7.4, TP5.1, U2.30 (PA5)
SPI2_MISO: J9.16, U2.53 (PB14)
SPI2_MOSI: J9.15, U2.54 (PB15)
SPI2_SCK: J9.17, U2.52 (PB13)
SYS_JTCK-SWCLK: J2.4, U2.76 (PA14)
SYS_JTDO-TRACESWO: J2.6, U2.89 (PB3)
SYS_JTMS-SWDIO: J2.2, U2.72 (PA13)
UART2_RX: J9.7, U2.87 (PD6)
UART2_TX: J9.6, U2.86 (PD5)
USB_CONN_D+: R15.2, U3.3 (I/O2)
USB_CONN_D-: R16.1, U3.1 (I/O1)
USB_D+: U2.71 (PA12), U3.4 (I/O2)
USB_D-: U2.70 (PA11), U3.6 (I/O1)
VFB1: IC1.7 (VFB1), R1.2, R2.1
VFB2: IC1.10 (VFB2), R5.2, R6.1
VIN: C5.1, C6.1, IC1.1 (VIN1), IC1.16 (VIN2), J1.1, J10.16, J10.17, R3.1

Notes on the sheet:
VIN {7.4V-11.1V}
USB
I2C Devices
X OSC
Breakout Headers
Serial Wire Debug
SPI Devices
Rail Creation
Power Conditioning

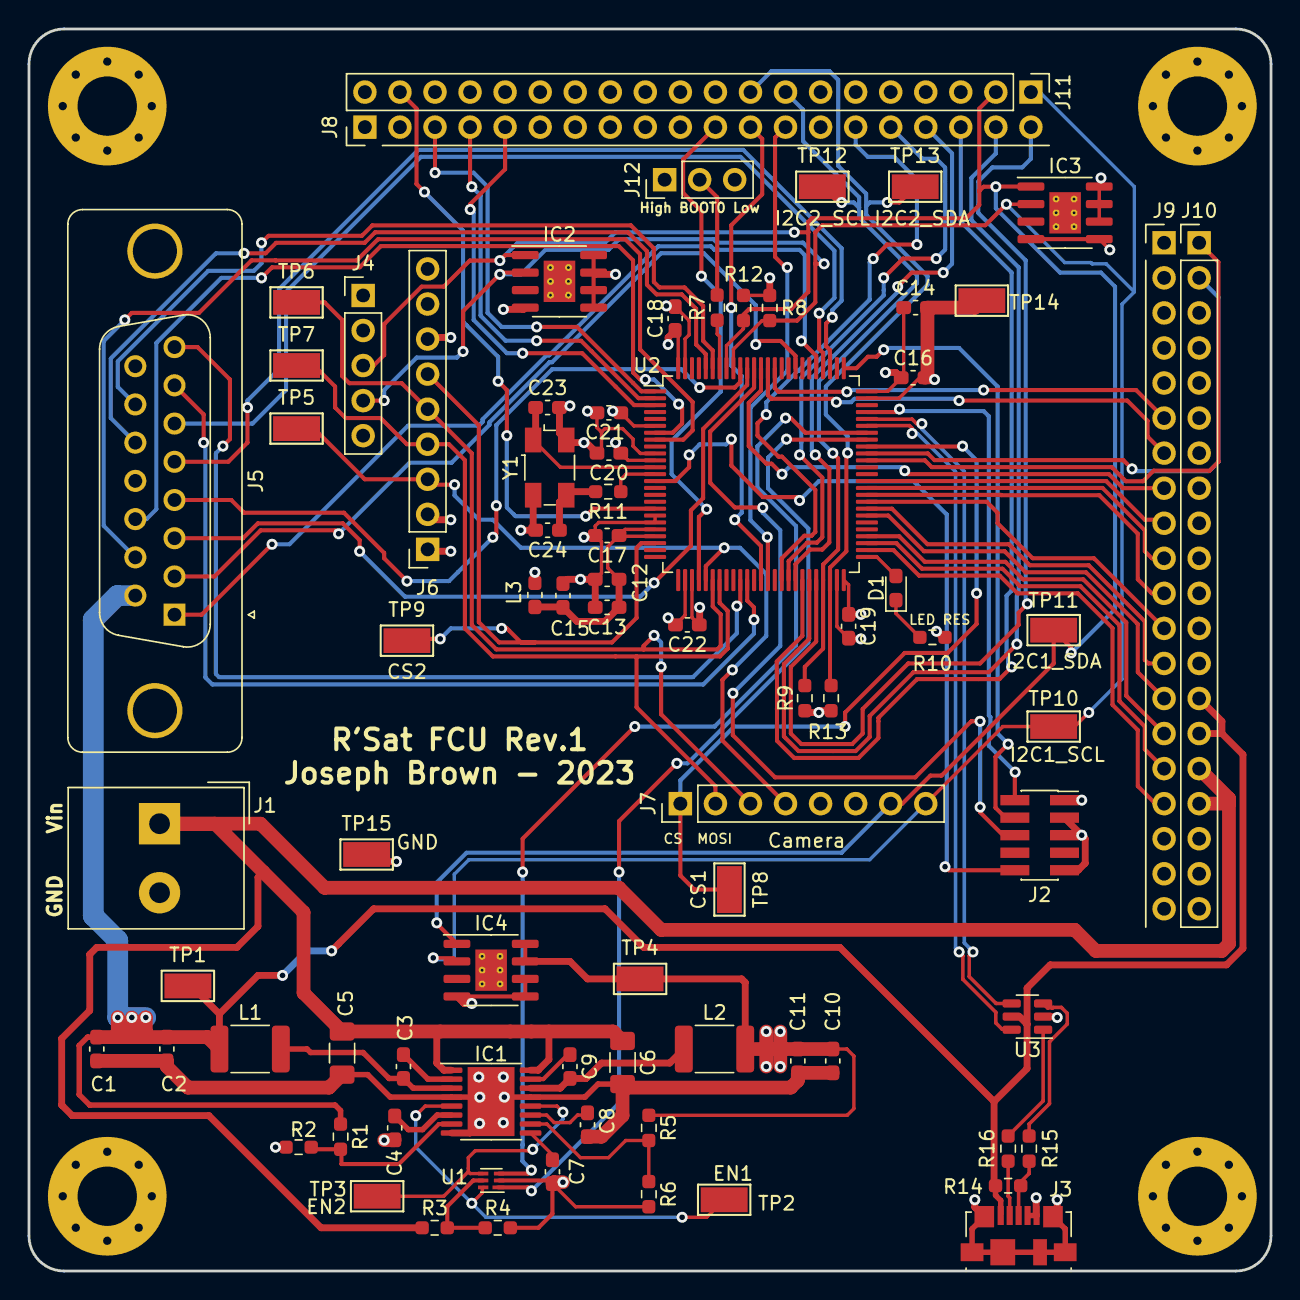
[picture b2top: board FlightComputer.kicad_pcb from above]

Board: 4 copper layers, 90.0 x 90.0 mm, 83 parts (0 on the bottom side), 84 nets.

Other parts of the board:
TP15: GNDA; TestPoint_Keystone_5015_Micro-Minature

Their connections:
GND: TP15.1; also elsewhere on the board

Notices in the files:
parts and their libraries:
Copyright 2021 Accelerated Designs. All rights reserved.
